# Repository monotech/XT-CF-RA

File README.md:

Monotech XT-CF Rev1.0 ReadMe
----------------------------

8-bit ISA CompactFlash interface + Boot ROM (two separate functions that can be used individually).

Documentation for the switches can be found on the rear silkscreen.

Credit:
-------
Design uses schematic from Sergey Kiselev, with a few small changes to switches, 32K ROM support, and PCB from scratch to suit my brackets.\
www.malinov.com/Home/sergeys-projects/xt-cf-lite

XT-IDE Universal BIOS\
www.xtideuniversalbios.org  
www.xtideuniversalbios.org/binaries  
Use the latest working binary that includes XTIDECFG.COM (config utility), ide_xt.bin (8086/8088), ide_xtp.bin (80186/V20/V30 and up).

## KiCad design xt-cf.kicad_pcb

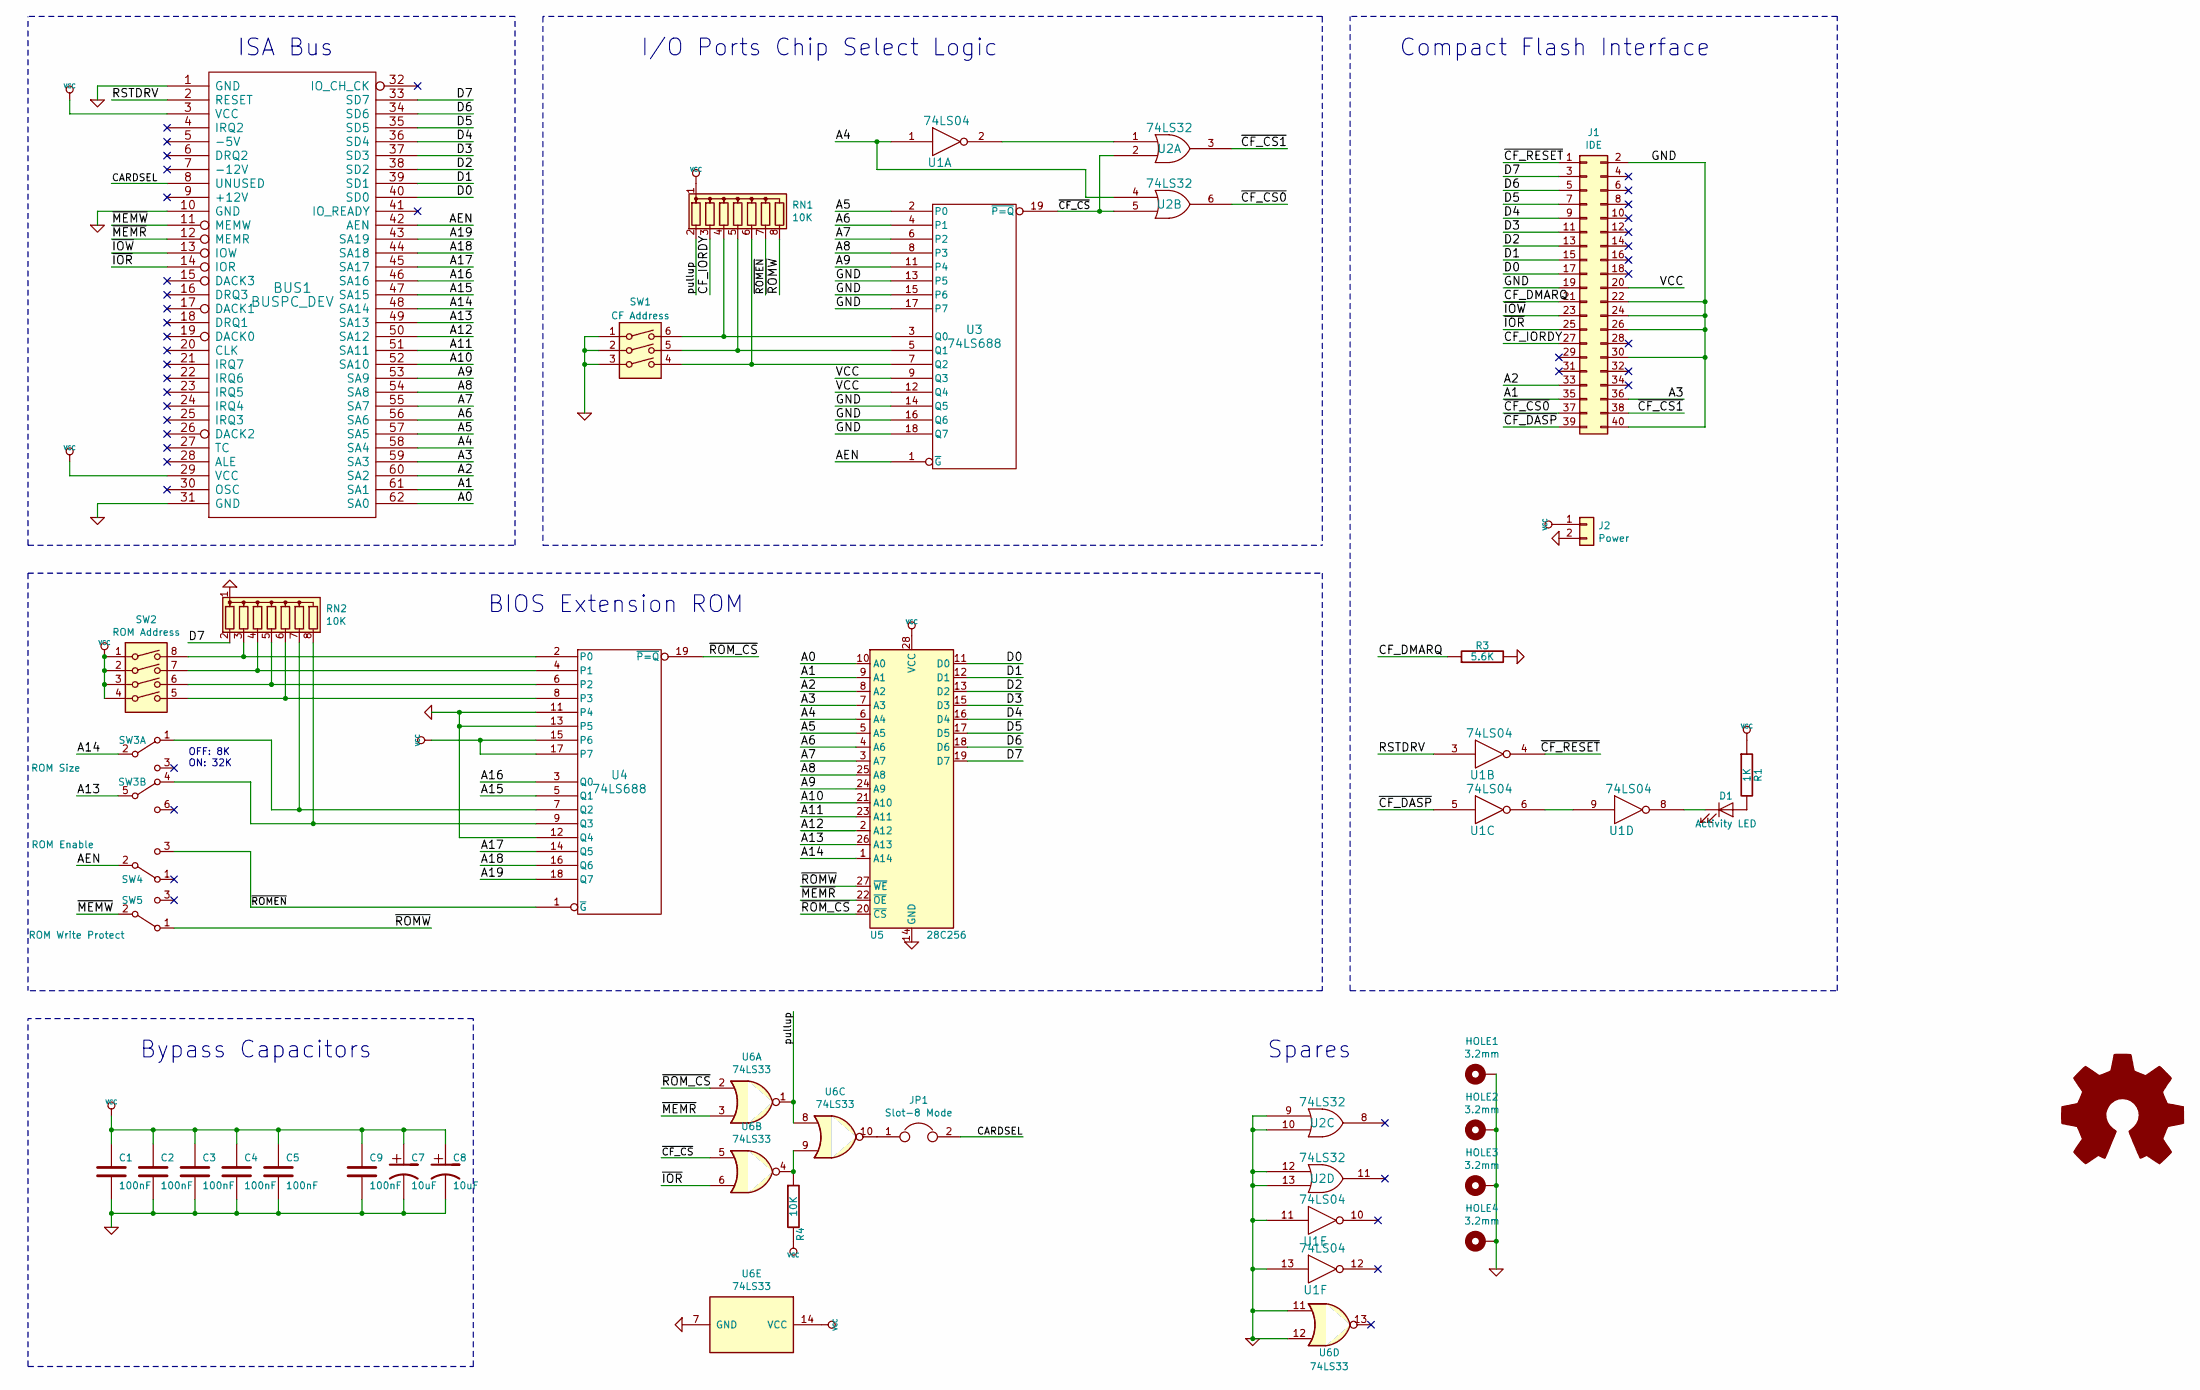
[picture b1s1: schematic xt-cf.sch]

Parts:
BUS1: BUSPC_DEV; ISA-8BIT-XT-CF
C1, C2, C3, C4, C5: 100nF; C_Disc_D4.3mm_W1.9mm_P5.00mm
C7, C8: 10uF; C_Disc_D4.3mm_W1.9mm_P5.00mm
C9: 100nF; C_0805_2012Metric_Pad1.15x1.40mm_HandSolder
D1: Activity LED; PinHeader_1x02_P2.54mm_Horizontal
HOLE1, HOLE2, HOLE3, HOLE4: 3.2mm; MountingHole_3.2mm_M3_Pad
J1: IDE; PinSocket_2x20_P2.54mm_Vertical
J2: Power; PinSocket_1x02_P2.54mm_Vertical
JP1: Slot-8 Mode; PinHeader_1x02_P2.54mm_Vertical
LOGO1: Logo_Open_Hardware_Large; Monotech Logo 12.7mm
R1: 1K; R_Axial_DIN0204_L3.6mm_D1.6mm_P5.08mm_Horizontal
R3: 5.6K; R_Axial_DIN0204_L3.6mm_D1.6mm_P5.08mm_Horizontal
R4: 10K; R_0805_2012Metric_Pad1.15x1.40mm_HandSolder
RN1, RN2: 10K; R_Array_SIP8
SW1: CF Address; SW_DIP_SPSTx03_Slide_9.78x9.8mm_W7.62mm_P2.54mm
SW2: ROM Address; SW_DIP_SPSTx04_Slide_9.78x12.34mm_W7.62mm_P2.54mm
SW3: ROM Size; SW_MS-22D18G2
SW4: ROM Enable; SW_CuK_OS102011MA1QN1_SPDT_Angled
SW5: ROM Write Protect; SW_CuK_OS102011MA1QN1_SPDT_Angled
U1: 74LS04; DIP-14_W7.62mm
U2: 74LS32; DIP-14_W7.62mm
U3, U4: 74LS688; DIP-20_W7.62mm
U5: 28C256; DIP-28_W15.24mm_Socket
U6: 74LS33; SOIC-14_3.9x8.7mm_P1.27mm

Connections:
/A0: BUS1.62 (SA0), U5.10 (A0)
/A1: BUS1.61 (SA1), J1.35, U5.9 (A1)
/A2: BUS1.60 (SA2), J1.33, U5.8 (A2)
/A3: BUS1.59 (SA3), J1.36, U5.7 (A3)
/A4: BUS1.58 (SA4), U1.1, U2.4, U5.6 (A4)
/A5: BUS1.57 (SA5), U3.2 (P0), U5.5 (A5)
/A6: BUS1.56 (SA6), U3.4 (P1), U5.4 (A6)
/A7: BUS1.55 (SA7), U3.6 (P2), U5.3 (A7)
/A8: BUS1.54 (SA8), U3.8 (P3), U5.25 (A8)
/A9: BUS1.53 (SA9), U3.11 (P4), U5.24 (A9)
/A10: BUS1.52 (SA10), U5.21 (A10)
/A11: BUS1.51 (SA11), U5.23 (A11)
/A12: BUS1.50 (SA12), U5.2 (A12)
/A13: BUS1.49 (SA13), SW3.5 (B), U5.26 (A13)
/A14: BUS1.48 (SA14), SW3.2 (B), U5.1 (A14)
/A15: BUS1.47 (SA15), U4.5 (Q1)
/A16: BUS1.46 (SA16), U4.3 (Q0)
/A17: BUS1.45 (SA17), U4.14 (Q5)
/A18: BUS1.44 (SA18), U4.16 (Q6)
/A19: BUS1.43 (SA19), U4.18 (Q7)
/AEN: BUS1.42 (AEN), SW4.2 (B), U3.1 (~G)
/CARDSEL: BUS1.8 (UNUSED), JP1.2
/CF_DMARQ: J1.21, R3.1
/CF_IORDY: J1.27, RN1.3 (R2)
/D0: BUS1.40 (SD0), J1.17, U5.11 (D0)
/D1: BUS1.39 (SD1), J1.15, U5.12 (D1)
/D2: BUS1.38 (SD2), J1.13, U5.13 (D2)
/D3: BUS1.37 (SD3), J1.11, U5.15 (D3)
/D4: BUS1.36 (SD4), J1.9, U5.16 (D4)
/D5: BUS1.35 (SD5), J1.7, U5.17 (D5)
/D6: BUS1.34 (SD6), J1.5, U5.18 (D6)
/D7: BUS1.33 (SD7), J1.3, RN2.2 (R1), U5.19 (D7)
/RSTDRV: BUS1.2 (RESET), U1.3
/pullup: RN1.2 (R1), U6.1, U6.8
/~CF_CS: U2.2, U2.5, U3.19 (~P=Q), U6.5
/~CF_CS0: J1.37, U2.6
/~CF_CS1: J1.38, U2.3
/~CF_DASP: J1.39, U1.5
/~CF_RESET: J1.1, U1.4
/~IOR: BUS1.14 (IOR), J1.25, U6.6
/~IOW: BUS1.13 (IOW), J1.23
/~MEMR: BUS1.12 (MEMR), U5.22 (~OE), U6.3
/~MEMW: BUS1.11 (MEMW), SW5.2 (B)
/~ROMEN: RN1.7 (R6), SW4.3 (C), U4.1 (~G)
/~ROMW: RN1.8 (R7), SW5.1 (A), U5.27 (~WE)
/~ROM_CS: U4.19 (~P=Q), U5.20 (~CS), U6.2
GND: BUS1.1 (GND), BUS1.10 (GND), BUS1.31 (GND), C1.2, C2.2, C3.2, C4.2, C5.2, C7.2, C8.2, C9.2, HOLE1.1, HOLE2.1, HOLE3.1, HOLE4.1, J1.2, J1.19, J1.22, J1.24, J1.26, J1.30, J1.40, J2.2, R3.2, RN2.1 (common), SW1.1, SW1.2, SW1.3, U1.7 (GND), U1.11, U1.13, U2.7 (GND), U2.9, U2.10, U2.12, U2.13, U3.10 (GND), U3.13 (P5), U3.14 (Q5), U3.15 (P6), U3.16 (Q6), U3.17 (P7), U3.18 (Q7), U4.10 (GND), U4.11 (P4), U4.12 (Q4), U4.13 (P5), U5.14 (GND), U6.7 (GND), U6.11, U6.12
unnamed: D1.1 (K), U1.8
unnamed: D1.2 (A), R1.2
unnamed: JP1.1, U6.10
unnamed: R4.1, U6.4, U6.9
unnamed: RN1.4 (R3), SW1.6, U3.3 (Q0)
unnamed: RN1.5 (R4), SW1.5, U3.5 (Q1)
unnamed: RN1.6 (R5), SW1.4, U3.7 (Q2)
unnamed: RN2.3 (R2), SW2.8, U4.2 (P0)
unnamed: RN2.4 (R3), SW2.7, U4.4 (P1)
unnamed: RN2.5 (R4), SW2.6, U4.6 (P2)
unnamed: RN2.6 (R5), SW2.5, U4.8 (P3)
unnamed: RN2.7 (R6), SW3.1 (A), U4.7 (Q2)
unnamed: RN2.8 (R7), SW3.4 (A), U4.9 (Q3)
unnamed: U1.2, U2.1
unnamed: U1.6, U1.9
VCC: BUS1.3 (VCC), BUS1.29 (VCC), C1.1, C2.1, C3.1, C4.1, C5.1, C7.1, C8.1, C9.1, J1.20, J2.1, R1.1, R4.2, RN1.1 (common), SW2.1, SW2.2, SW2.3, SW2.4, U1.14 (VCC), U2.14 (VCC), U3.9 (Q3), U3.12 (Q4), U3.20 (VCC), U4.15 (P6), U4.17 (P7), U4.20 (VCC), U5.28 (VCC), U6.14 (VCC)

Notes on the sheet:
Spares
ISA Bus
BIOS Extension ROM
Bypass Capacitors
I/O Ports Chip Select Logic
Compact Flash Interface
OFF: 8K ON: 32K

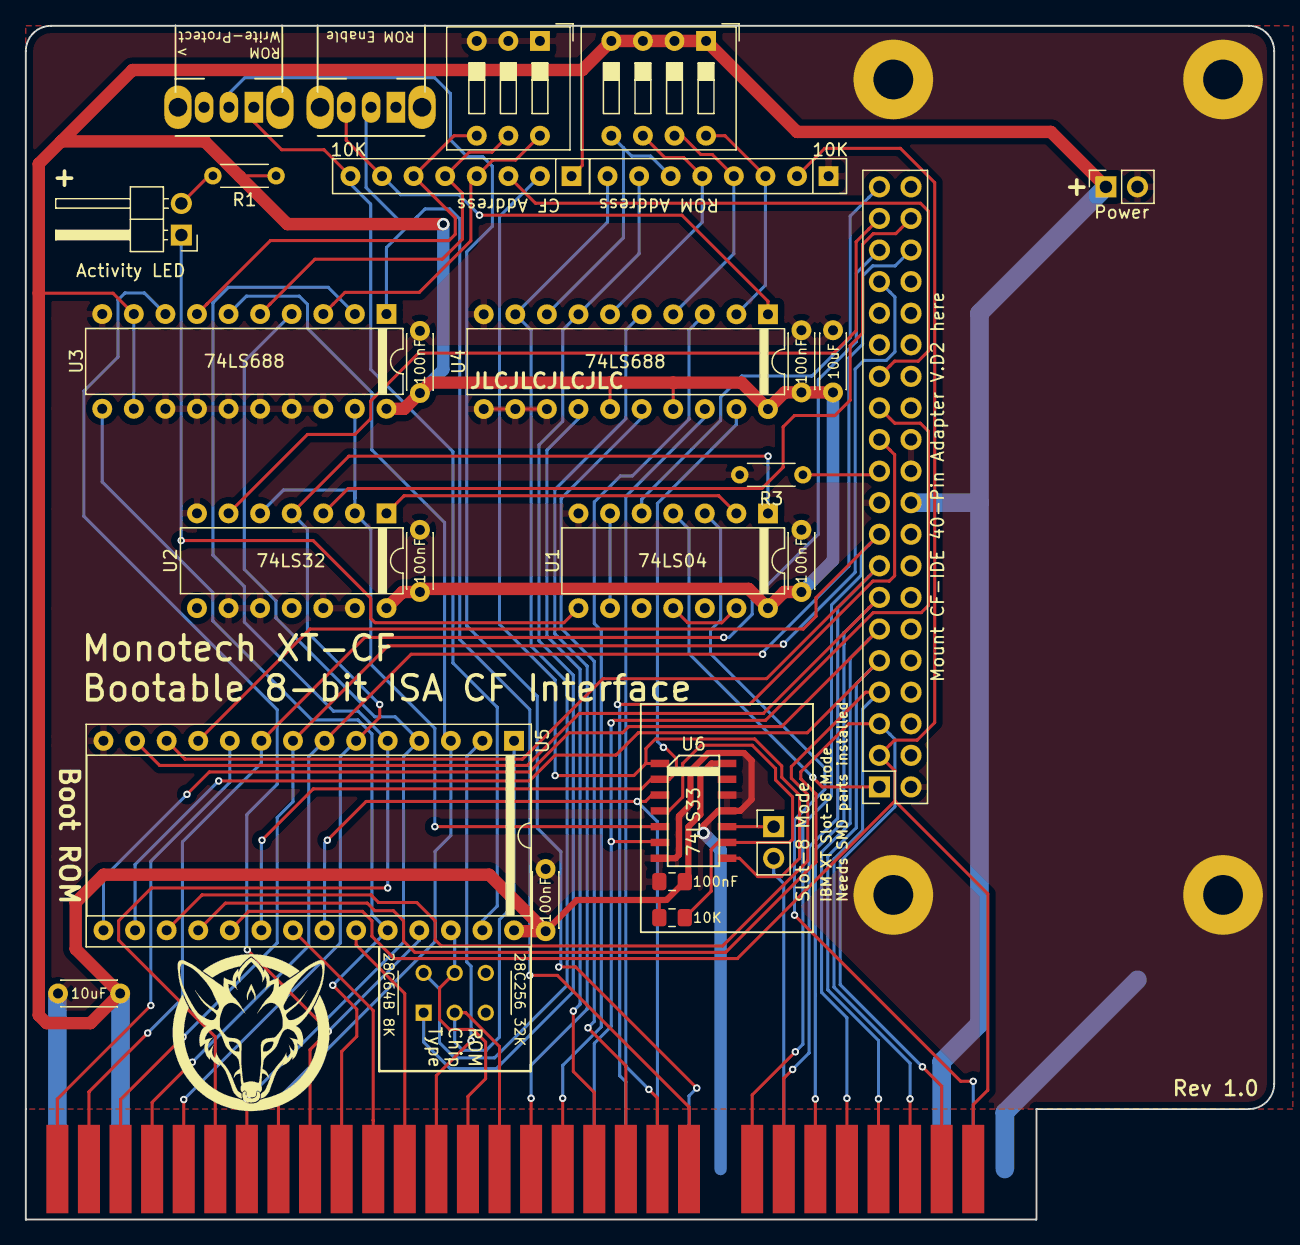
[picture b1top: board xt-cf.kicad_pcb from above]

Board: 2 copper layers, 100.4 x 96.0 mm, 34 parts (0 on the bottom side), 63 nets.

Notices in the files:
xt-cf.kicad_pcb:
GPL v3
